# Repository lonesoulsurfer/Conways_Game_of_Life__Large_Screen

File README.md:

**YouTube:** https://studio.youtube.com/video/bC17AgROvXw/edit

**Instructable:** https://www.instructables.com/Conways-Game-of-Life-XL-Screen-Raspberry-Pi-Projec/

### ▶ [Try the Web Simulator](https://htmlpreview.github.io/?https://github.com/lonesoulsurfer/Conways_Game_of_Life__Large_Screen/blob/main/Game_of_Life_Simulation.html) — no hardware required, runs in your browser

---

## Contents

- [Hardware & Setup](#hardware--setup)
- [Web Simulator](#web-simulator)
- [Main Menu](#main-menu)
- [Standard Controls](#standard-controls-conway--alt-games--rule-explorer)
- [Conway's Life Modes](#conways-life-modes)
- [Alternative Cellular Automata (Alt Games)](#alternative-cellular-automata-alt-games)
- [Lenia Sandbox](#lenia-sandbox)
- [Tools Menu](#tools-menu)
- [Arcade Games](#arcade-games)

---

## Hardware & Setup

The device runs on a Raspberry Pi Pico / RP2040 connected to a 3.5" ST7796S/ST7796U TFT display (480×320 pixels) via SPI. Six buttons handle all navigation and gameplay: Up, Down, Left, Right, SET (A), and B. A buzzer on GPIO 26 provides sound effects and music. Display brightness is PWM-controlled, and all settings (sound, volume, brightness) are saved to EEPROM so they persist between power cycles.

## Web Simulator

Don't have the hardware? [**Game_of_Life_Simulation.html**](Game_of_Life_Simulation.html) is a single-file, browser-based recreation of the firmware that runs on any modern desktop browser — [click here to launch it directly](https://htmlpreview.github.io/?https://github.com/lonesoulsurfer/Conways_Game_of_Life__Large_Screen/blob/main/Game_of_Life_Simulation.html), or download the file and open it locally.

It's a faithful port of the firmware's menu logic and simulation rules, built directly from this repo's source — not a from-scratch reimplementation. It covers:

- The full Conway's Life menu shell: Presets, Random, Symmetric, Custom, and Rule Explorer (including the Custom Rule bit editor)
- All seven Alt Games automata: Brian's Brain, Day & Night, Seeds, Cyclic CA, Wireworld, Langton's Ant, and Wolfram 1D
- The Lenia Sandbox, with its own live parameter panel and control scheme
- The Tools menu (Grid Lines, Population Counter, Trail Mode, Colour Mode, Toroidal World)

On-screen buttons mirror the physical Up/Down/Left/Right/A/B layout, and the same controls also work from a keyboard (arrow keys, A/Enter/Space, B) — including two-button combos like Up+Down for colour mode.

**Not included:** Arcade Games (Star Wars, Breakout Beyond, Gyruss) and hardware-only features like sound and screen brightness, which don't have a meaningful browser equivalent.

## Main Menu

On startup the device boots directly into the main scrolling menu with eight sections:

| # | Section | Description |
|---|---|---|
| 1 | Presets | Hand-crafted Conway's Life patterns |
| 2 | Random | Randomised Conway's Life |
| 3 | Symmetric | Procedurally generated symmetric patterns |
| 4 | Custom | Draw your own pattern |
| 5 | Rule Explorer | Define custom birth/survival rules |
| 6 | Alt Games | Alternative cellular automata (including Lenia Sandbox) |
| 7 | Tools | Display and simulation settings |
| 8 | Arcade | Three built-in arcade games |

Navigate with Up/Down, select with SET, go back with B.

## Standard Controls (Conway / Alt Games / Rule Explorer)

These controls apply to Conway's Life modes, Rule Explorer, and every Alt Games automaton except Lenia Sandbox, which has its own control scheme. See the [Lenia Sandbox](#lenia-sandbox) section.

| Button | Action |
|---|---|
| Up | Increase simulation speed |
| Down | Decrease simulation speed |
| Left | Cycle cell size (Small 3px, Normal 4px, Large 8px) |
| Right | Reset / regenerate the current pattern |
| Up + Down | Toggle colour mode |
| SET (hold) | Start simulation from edit mode |
| SET (hold, running) | Return to edit mode (Custom / Seeds / Brian's Brain only) |
| B (short press) | Return to menu |
| B (hold ~1 second) | Show/hide rules and information panel |

## Conway's Life Modes

### Presets (13 patterns)

Press SET once to open a preset, then A to start the simulation. While paused you can press Left to change cell size (the pattern rescales and redraws) or Right to reset it back to its starting state.

| # | Pattern | Notes |
|---|---|---|
| 1 | Coe Ship | Puffer-type spaceship that leaves debris trails |
| 2 | Gosper Gun | The first glider gun ever discovered, period 30 |
| 3 | Diamond | Symmetric expanding diamond pattern |
| 4 | Achim p144 | Rare period-144 oscillator |
| 5 | 56P6H1V0 | High-period spaceship |
| 6 | LWSS Convoy | Three Lightweight Spaceships in formation |
| 7 | MWSS | Middleweight Spaceship, 8 cells, speed c/2 |
| 8 | Pulsar | Period-3 oscillator with 4-fold symmetry, 48 cells |
| 9 | Pentadecathlon | 15-cell oscillator made from a modified 10-cell row |
| 10 | R-Pentomino | 5-cell seed that runs for 1,103 generations |
| 11 | Acorn | 7-cell methuselah running 5,206 generations |
| 12 | Simkin Gun | Smallest known glider gun, 36 cells, period 120 |
| 13 | Queen Bee | Period-30 oscillator, the first of its kind ever found |

### Random

Fills the board with random live cells at approximately 30% density. Immediately starts running. Press Right to re-randomise.

### Symmetric

Generates a random pattern with one of three symmetry types (vertical, horizontal, or rotational) in small, medium, or large sizes. Good for producing structured chaos.

### Custom

Puts the board into edit mode with a blinking red crosshair cursor. Move the cursor with Up/Down/Left/Right. Press SET to toggle a cell on or off. When happy with your pattern, hold SET for about a second to start the simulation. Hold SET again to return to edit mode. Press B to go back to the menu.

### Rule Explorer

Define your own cellular automaton by setting custom Birth (B) and Survival (S) rules, the same notation used by Life (B3/S23). Choose from 12 built-in rule presets or enter your own bit-by-bit. The simulation runs with your rules applied to a random starting board.

**Included preset rules:** High Life, 34 Life, Diamoeba, Replicator, Long Life, Maze, Coral, 2x2, Dry Life, Amoeba, Coagulate, Gnarl

## Alternative Cellular Automata (Alt Games)

**Brian's Brain.** A three-state automaton (On, Dying, Off) producing a constantly moving stream of light-speed "signals." Choose from small, medium, large, or random seedings, or draw a custom starting pattern.

**Day & Night** (B3678/S34678). A symmetric ruleset where dead and live regions are interchangeable. Dense regions survive and grow in a way that mirrors the original, creating organic, blob-like patterns.

**Seeds** (B2/S). Every live cell dies every generation but any dead cell with exactly two live neighbours is born. Creates explosive, constantly moving patterns that never stabilise.

**Cyclic CA.** A multi-state automaton where cells cycle through states 0→1→2→…→N→0. Cells advance only when they have a neighbour in the next state. Produces rotating spiral waves. Choose small, medium, or large seedings.

**Wireworld.** A four-state automaton (Empty, Wire, Electron Head, Electron Tail) that models digital logic circuits. Electrons travel along wires, interact at junctions, and can form AND gates and clocks. The built-in demo includes a working circuit layout.

**Langton's Ant.** A single ant on a grid follows two rules: turn right on a white cell and flip it black, turn left on a black cell and flip it white. After roughly 10,000 chaotic steps it spontaneously builds a repeating diagonal "highway." Toggle age-colour mode with Up+Down to see a heat map of how often each cell has been visited.

**Wolfram 1D Automata.** One-dimensional elementary cellular automata: a single row of cells evolves downward according to one of 255 possible rules. Each rule produces a unique pattern, from pure chaos (Rule 30) to the Sierpinski triangle (Rule 90) to a Turing-complete system (Rule 110). Seven named presets are provided, or you can enter any rule number directly.

**Lenia Sandbox.** A continuous cellular automaton with its own control scheme, described below.

## Lenia Sandbox

Unlike every automaton above, Lenia isn't discrete. Cells hold a value from 0-255 instead of a simple on/off state, and each step blends that value with a weighted neighbourhood (the kernel) instead of applying binary birth/survival rules. The result is smooth, organic life forms that grow and drift.

The play area occupies the right two-thirds of the screen, with a live parameter panel on the left third.

**Parameters** (adjust with Up/Down to select, Left/Right to change value):

| Parameter | Meaning |
|---|---|
| Mu | Growth centre: the neighbourhood value that produces the strongest growth |
| Sigma | Growth width: how forgiving that target value is |
| Radius | How far each cell looks at its neighbours |
| Speed | How much each step nudges the field (time step / dt) |

**Controls:**

| Button | Action |
|---|---|
| Up / Down | Select a parameter row |
| Left / Right | Adjust the selected parameter |
| SET (A) | Reseed the board with fresh random blobs |
| Up + Down | Toggle colour scheme (blue/cyan/white or fire) |
| B (short tap) | Return to the Alt Games menu |
| B (hold ~1 second) | Show/hide the rules and parameter info panel |
| SET + B (hold ~1 second) | Full reset: parameters back to defaults, fresh seed |

Honours the shared Toroidal World setting from the Tools menu (wrap edges on/off) and the Auto-Cycle screensaver tool (periodically reseeds on its own, same as the other automata).

## Tools Menu

**Grid Lines.** Overlays a faint grid matching the current cell size.

**Population Counter.** Shows live cell count and generation number during simulation.

**Trail Mode.** Dying cells leave a soft 20-step fade trail rather than disappearing instantly.

**Colour Mode.** Age-based colouring; young cells are one colour, older cells shift through the spectrum.

**Toroidal World.** When on, edges wrap around so the board is a torus. When off, edges are hard boundaries.

**Brightness.** Four levels: 25%, 50%, 75%, 100%.

**Auto-Cycle / Screensaver.** Automatically switches to a random game mode or Wolfram rule every 300 generations. Useful as a display piece.

**Sound settings.** Enabled/disabled, three volume levels. Also accessible here and saved to EEPROM.

## Arcade Games

Accessed from main menu item 8. Three games are available. In all three, press A + B together at any time to exit directly back to the main menu.

### Star Wars

A first-person Star Wars game inspired by the 80's arcade game. Progress through multiple stages: Womp Rat Training, Space Battle, Death Star Approach, Surface Run, and the Exhaust Port shot. Features full Star Wars music (Main Theme, Binary Sunset, Imperial March, Victory Fanfare), sound effects, TIE fighters, laser cannons, proton torpedoes, and a dramatic finale sequence. Press B on the title screen to exit.

| Button | Action |
|---|---|
| Up/Down/Left/Right | Move crosshair / pilot ship |
| SET | Fire |
| A + B | Exit to main menu |
| Up + Down (title screen) | Enter games menu to play any of the games or watch the cinematic shorts |

### Breakout Beyond

A feature-rich Breakout variant with a neon aesthetic. The paddle sits at the bottom, bricks at the top. Features include combo multipliers, spin physics, multiball, shield power-ups, bomb bricks, and hard bricks across 20 levels.

| Button | Action |
|---|---|
| Left/Right | Move paddle |
| B | Speed boost |
| SET | Launch ball / pause |
| A + B (hold) | Exit to main menu |

### Gyruss

A circular shoot-em-up inspired by the 1983 Konami arcade classic. Your ship orbits around the edge of the screen shooting inward at waves of enemies that fly in formation patterns.

| Button | Action |
|---|---|
| Left/Right | Rotate ship around the ring |
| SET or B | Fire |
| Up (hold) | Smart bomb |
| A + B (hold) | Exit to main menu |

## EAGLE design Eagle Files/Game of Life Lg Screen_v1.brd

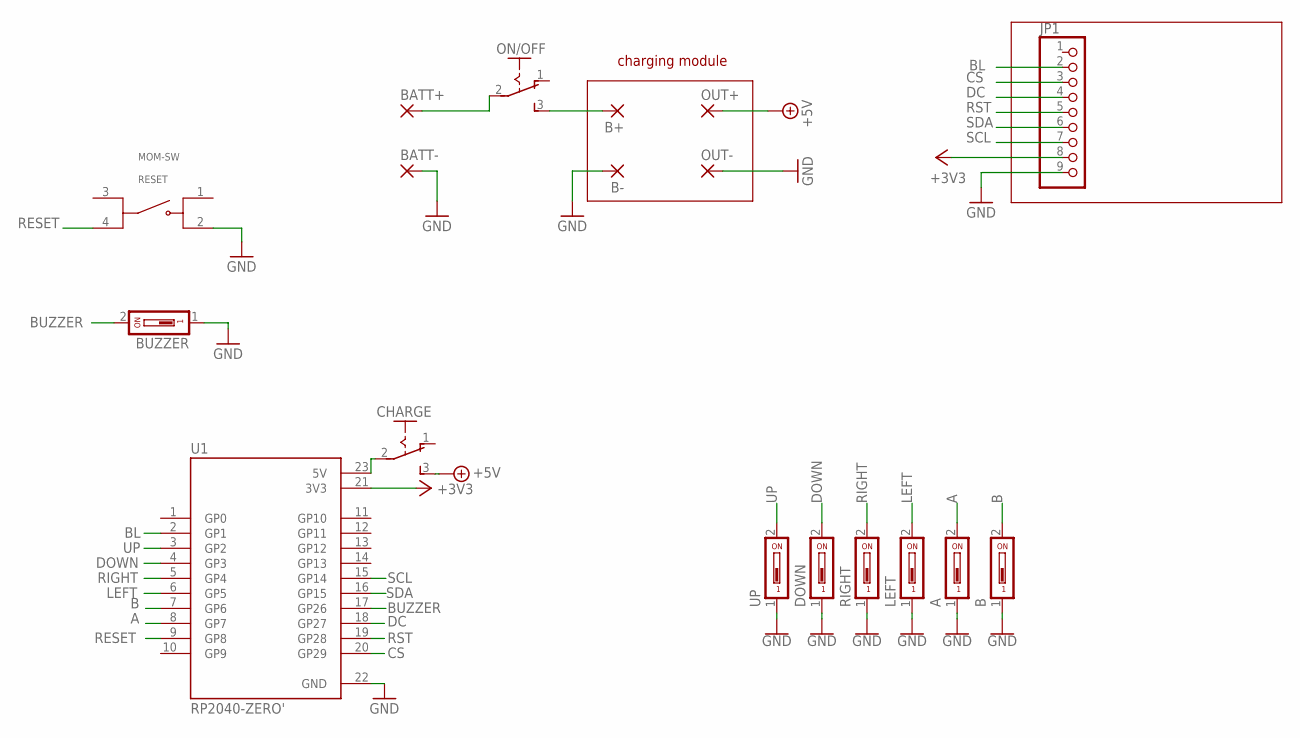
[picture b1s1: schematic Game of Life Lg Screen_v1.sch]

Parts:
A: DS01; DS-01
B: DS01; DS-01
B+: SMD5; SMD2,54-5,08
B-: SMD5; SMD2,54-5,08
BATT+: SMD5; SMD2,54-5,08
BATT-: SMD5; SMD2,54-5,08
BUZZER: DS01; DS-01
CHARGE: M251
DOWN: DS01; DS-01
JP1: PINHD-1X9; 1X09
LEFT: DS01; DS-01
ON/OFF: M251
OUT+: SMD5; SMD2,54-5,08
OUT-: SMD5; SMD2,54-5,08
RESET: MOM-SW; SW_TS18-5-25-SL-260-SMT-TR
RIGHT: DS01; DS-01
U1: RP2040-ZERO'; MODULE_RP2040-ZERO
UP: DS01; DS-01

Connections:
+3V3: JP1.8, U1.21 (3V3)
+5V: CHARGE.3 (S), OUT+.1
A: A.2, U1.8 (GP7)
B: B.2, U1.7 (GP6)
BL: JP1.2, U1.2 (GP1)
BUZZER: BUZZER.2, U1.17 (GP26)
CS: JP1.3, U1.20 (GP29)
DC: JP1.4, U1.18 (GP27)
DOWN: DOWN.2, U1.4 (GP3)
GND: A.1, B.1, B-.1, BATT-.1, BUZZER.1, DOWN.1, JP1.9, LEFT.1, OUT-.1, RESET.2, RIGHT.1, U1.22 (GND), UP.1
LEFT: LEFT.2, U1.6 (GP5)
unnamed: B+.1, ON/OFF.3 (S)
unnamed: CHARGE.2, U1.23 (5V)
unnamed: BATT+.1, ON/OFF.2
RESET: RESET.4, U1.9 (GP8)
RIGHT: RIGHT.2, U1.5 (GP4)
RST: JP1.5, U1.19 (GP28)
SCL: JP1.7, U1.15 (GP14)
SDA: JP1.6, U1.16 (GP15)
UP: U1.3 (GP2), UP.2

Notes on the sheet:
charging module

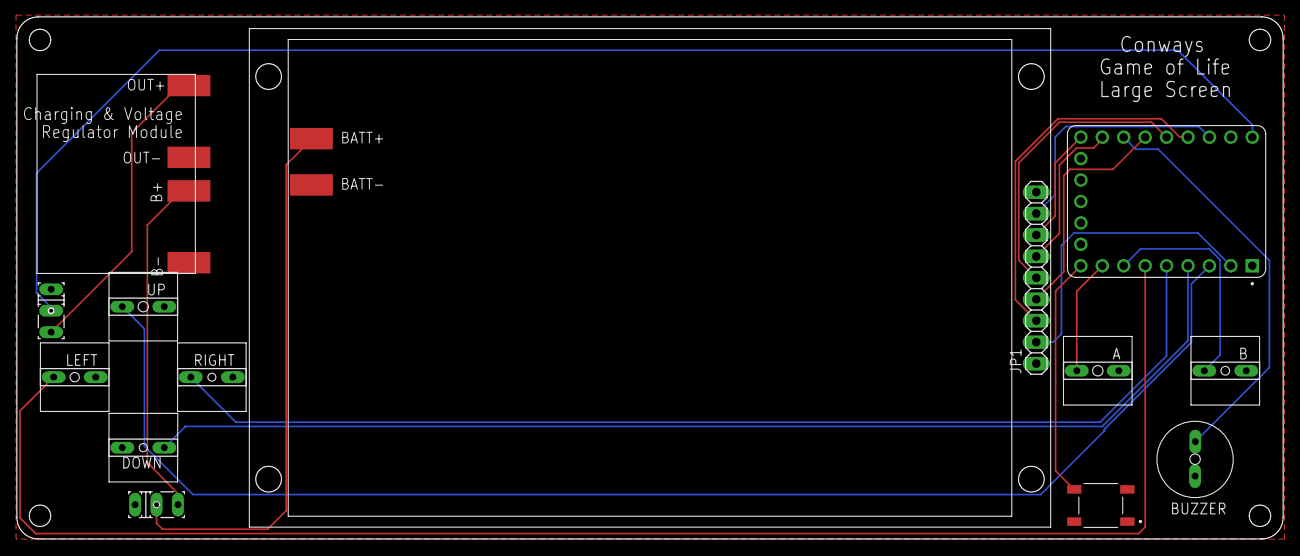
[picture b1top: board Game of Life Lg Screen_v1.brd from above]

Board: 2 copper layers, 150.1 x 61.9 mm, 18 parts (0 on the bottom side), 20 nets.

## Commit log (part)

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2026-03-19 Fix formatting in README.md for in-game controls
2026-03-19 Update README with images and external links
    Added images and links to YouTube and Instructable.
2026-03-19 Clean up image links in README
    Removed multiple image links from the README.
2026-03-19 Add Instructable link to README

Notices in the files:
parts and their libraries:
SparkFun-PowerSymbols: Licensing: Creative Commons ShareAlike 4.0 International - https://creativecommons.org/licenses/by-sa/4.0
